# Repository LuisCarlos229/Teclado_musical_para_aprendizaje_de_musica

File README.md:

# Teclado musical para aprendizaje de música
 
Teclado sintetizador de bajo costo basado en ESP32, pensado para que niños aprendan música mediante un **modo aprendizaje** que guía la ejecución con LEDs.
 
Proyecto realizado en el marco de la asignatura **Proyecto Electrónico** de la Facultad de Ingeniería (FIO) – Universidad Nacional de Misiones (UNaM).

---
 
## Objetivos
 
Los objetivos planteados por la cátedra son:
 
- Diseñar y construir un teclado musical para el aprendizaje de música en niños, con tecnología transferible, de muy bajo costo y sin licencias de uso.
- Generar la documentación necesaria para su reproducción física.
- Emitir sonidos propios.
- Permitir cambiar parámetros musicales.
## Características
 
- 32 teclas con síntesis DDS por wavetables y salida I2S.
- Instrumentos activos: piano (Salamander Grand Piano) y guitarra.
- Modo aprendizaje: la tira LED WS2812B indica la nota a tocar y la canción avanza al ritmo del metrónomo, esperando a que se presione la nota correcta.
- Metrónomo configurable (3/4, 4/4, 5/4, 6/8, 7/8).
- Pantalla OLED con menú de configuración.
- Canciones permanentes en Flash y canciones adicionales en tarjeta SD (formato `.apr`).
## Estructura del repositorio
 
```
├── firmware/                       Código del ESP32 (ESP-IDF)
│   └── main/
│       ├── tasks/                  Tareas de FreeRTOS (audio, OLED, teclado, LEDs, SD, aprendizaje)
│       ├── notas/<instrumento>/    Wavetables y envolventes por instrumento (.h)
│       └── canciones/              Canciones permanentes en Flash (.h)
├── tools/
│   ├── wavetable_generator_octave/ Generación de wavetables y envolventes (Octave)
│   └── midi_processor_colab/       Conversión MIDI → .apr / .h (Python, Colab)
├── hardware/                       Proyecto KiCad: esquemáticos, PCB y lista de materiales
└── docs/                           manual de usuario e imágenes
```
 
## Flujo de trabajo
 
```
Grabaciones WAV/MP3 ──► Generador de wavetables (Octave) ──► .h de instrumentos ──┐
                                                                                  ├──► firmware (ESP-IDF) ──► ESP32
Archivos MIDI ────────► Procesador MIDI (Colab) ──► .h (Flash) ───────────────────┘
                                                └─► .apr ──► /APR en la tarjeta SD
```
 
## Requisitos
 
| Herramienta | Versión utilizada |
|---|---|
| ESP-IDF | v6.0.0 |
| GNU Octave | 11.1.0 (paquete `signal`) |
| Python | 3.x (Google Colab) con `mido` |
| KiCad | 9 |
 
## Uso rápido
 
### 1. Compilar y cargar el firmware
 
```bash
cd firmware
idf.py set-target esp32
idf.py build
idf.py -p PUERTO flash monitor
```
 
### 2. Generar wavetables de un instrumento
 
1. Colocar las grabaciones `.wav` del instrumento en `tools/wavetable_generator_octave/notas/<instrumento>/`.
2. Indicar el nombre del instrumento en `note_and_envelope_wavetable_generator.m` y ejecutarlo en Octave.
3. Copiar los `.h` generados en `notas/<instrumento>/salida_h/` a `firmware/main/notas/<instrumento>/`.
4. Agregar la carpeta en `INCLUDE_DIRS` de `firmware/main/CMakeLists.txt` y el instrumento en `firmware/main/tasks/Instrumentos.h`.
 
### 3. Convertir una canción MIDI
 
Abrir el notebook de [`tools/midi_processor_colab/`](tools/midi_processor_colab/) en Google Colab, cargar el `.mid` y elegir los canales a fusionar.
 
- Salida `.h` → `firmware/main/canciones/` (canción permanente en Flash).
- Salida `.apr` → carpeta `APR/` de la tarjeta SD.
### 4. Preparar la tarjeta SD
 
Formatear en FAT32, crear la carpeta `APR` en la raíz de la tarjeta y copiar ahí los `.apr` generados en el paso 3. El firmware busca las canciones en `/APR`.
 
## Hardware
 
| Bloque | Componentes principales |
|---|---|
| Control | ESP32 DevKit de 38 pines (CP2102) |
| Audio | DAC I2S PCM5102 + amplificador PAM8403 + altavoz de 4 Ω |
| Interfaz | Pantalla OLED I2C, tira LED WS2812B, expansor PCF8574 para pulsadores y LEDs |
| Teclado | Matriz de 32 teclas con diodos 1N4148 |
| Almacenamiento | Lector microSD |
| Alimentación | Fuente AC-DC Hi-Link HLK-10M05 (220 Vac → 5 V / 2 A) con fusible, regulador AMS1117-3.3 |
 
> **Precaución:** la placa trabaja con tensión de red de 220 Vac en la etapa de alimentación. Ensamblar y probar con las precauciones correspondientes, y montar el equipo en un gabinete cerrado antes de que lo usen niños.
 
El proyecto KiCad, el diagrama en bloques y la lista de materiales están en [`hardware/`](hardware/).
 
## Documentación
- Manual de usuario: [`docs/Manual_de_Usuario.pdf`](docs/Manual_de_Usuario.pdf).
## Créditos de muestras de audio
 
- **Salamander Grand Piano V3** – Alexander Holm ([sfzinstruments.github.io/pianos/salamander](https://sfzinstruments.github.io/pianos/salamander/)), licencia [CC BY 3.0](https://creativecommons.org/licenses/by/3.0/). Se usaron las muestras WAV de 16 bit a 44,1 kHz. Las wavetables y envolventes del firmware son obras derivadas: se extrajeron de esas grabaciones con el generador de Octave de este repositorio.
- **Philharmonia Sound Samples** – Philharmonia Orchestra ([philharmonia.co.uk/resources/sound-samples](https://philharmonia.co.uk/resources/sound-samples/)). Muestras de guitarra. Su licencia permite el uso libre, incluso comercial, siempre que las muestras no se vendan ni se distribuyan tal cual, ya sea como muestras o como instrumento de sampler.
> Por esta restricción, el repositorio **no incluye las grabaciones originales**. Solo incluye las wavetables y envolventes derivadas en formato `.h`. Para regenerarlas, descargá las muestras desde los sitios indicados y colocalas en `tools/wavetable_generator_octave/notas/<instrumento>/`.
 
## Créditos de canciones
 
### Canciones permanentes en Flash (`firmware/main/canciones/`)
 
| Canción | Origen de la melodía | Archivo |
|---|---|---|
| Estrellita | Melodía tradicional, dominio público | `cancion_estrellita.h` |
| Feliz cumpleaños | Melodía de *Good Morning to All*, M. J. y P. Hill, 1893, dominio público | `cancion_feliz_cumple.h` |
| Oda a la alegría | L. v. Beethoven, Sinfonía n.º 9, dominio público | `cancion_oda_alegria.h` |
| Para Elisa | L. v. Beethoven, WoO 59, dominio público | `cancion_para_elisa.h` |
 
## Bibliotecas de terceros
 
- **u8g2** – Oliver Kraus ([github.com/olikraus/u8g2](https://github.com/olikraus/u8g2)), licencia BSD de 2 cláusulas. Integrada mediante el componente ESP-IDF `nixy4/u8g2`.
- **led_strip** – Espressif Systems ([ESP Component Registry](https://components.espressif.com/components/espressif/led_strip)), licencia Apache 2.0.

## Autores

- Luis Carlos Hubner – [@LuisCarlos229](https://github.com/LuisCarlos229)
- Matias Emanuel Richart - [@MatiasRichart](https://github.com/MatiasRichart)

Cátedra de Proyecto Electrónico – FIO, UNaM.

## Licencias

Este proyecto se publica bajo licencias abiertas que permiten su uso, copia,
modificación, fabricación y comercialización sin pago de regalías:

| Contenido | Licencia | Archivo |
|---|---|---|
| Firmware ESP-IDF, scripts de Octave y Python | MIT | [LICENSE](LICENSE) |
| Hardware: esquemáticos, PCB, fabricación, BOM | CERN-OHL-P-2.0 | [hardware/LICENSE](hardware/LICENSE) |
| Documentación: manuales, guías, imágenes | CC BY 4.0 | [docs/LICENSE](docs/LICENSE) |
| Materiales de terceros: muestras de audio, librerías | Licencias propias | [NOTICE.md](NOTICE.md) |

Salvo que una carpeta tenga su propio archivo LICENSE, todo el contenido
original de este repositorio se publica bajo la licencia MIT.

## Aviso de responsabilidad

Este proyecto es un prototipo académico desarrollado en la Facultad de
Ingeniería de la Universidad Nacional de Misiones. Se entrega "tal cual",
sin garantía de ningún tipo. En la máxima medida permitida por la ley, los
autores no se responsabilizan por daños derivados de su fabricación, uso o
mal uso.

El dispositivo no está certificado como juguete según la normativa vigente.
Quien lo fabrique o distribuya es responsable de su seguridad y del
cumplimiento de las normas aplicables. Se recomienda su uso bajo
supervisión de un adulto.

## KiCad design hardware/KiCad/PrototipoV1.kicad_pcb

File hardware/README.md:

# Hardware — Teclado musical para aprendizaje de música

SPDX-License-Identifier: CERN-OHL-P-2.0
Copyright 2026 Luis Carlos Hubner, Matias Emanuel Richart
Source location: https://github.com/LuisCarlos229/Teclado_musical_para_aprendizaje_de_musica
Revisión: PrototipoV1

This source describes Open Hardware and is licensed under the CERN-OHL-P v2.

You may redistribute and modify this documentation and make products using it
under the terms of the CERN-OHL-P v2 (https://cern.ch/cern-ohl).

This documentation is distributed WITHOUT ANY EXPRESS OR IMPLIED WARRANTY,
INCLUDING OF MERCHANTABILITY, SATISFACTORY QUALITY AND FITNESS FOR A
PARTICULAR PURPOSE. Please see the CERN-OHL-P v2 for applicable conditions.

---

Los archivos de esta carpeta (esquemáticos y PCB en KiCad, archivos de
fabricación, lista de materiales y diseños mecánicos) se publican bajo la
licencia CERN-OHL-P v2, cuyo texto completo está en el archivo LICENSE de
esta misma carpeta. Pueden usarse, modificarse, fabricarse y comercializarse
libremente, conservando este aviso.

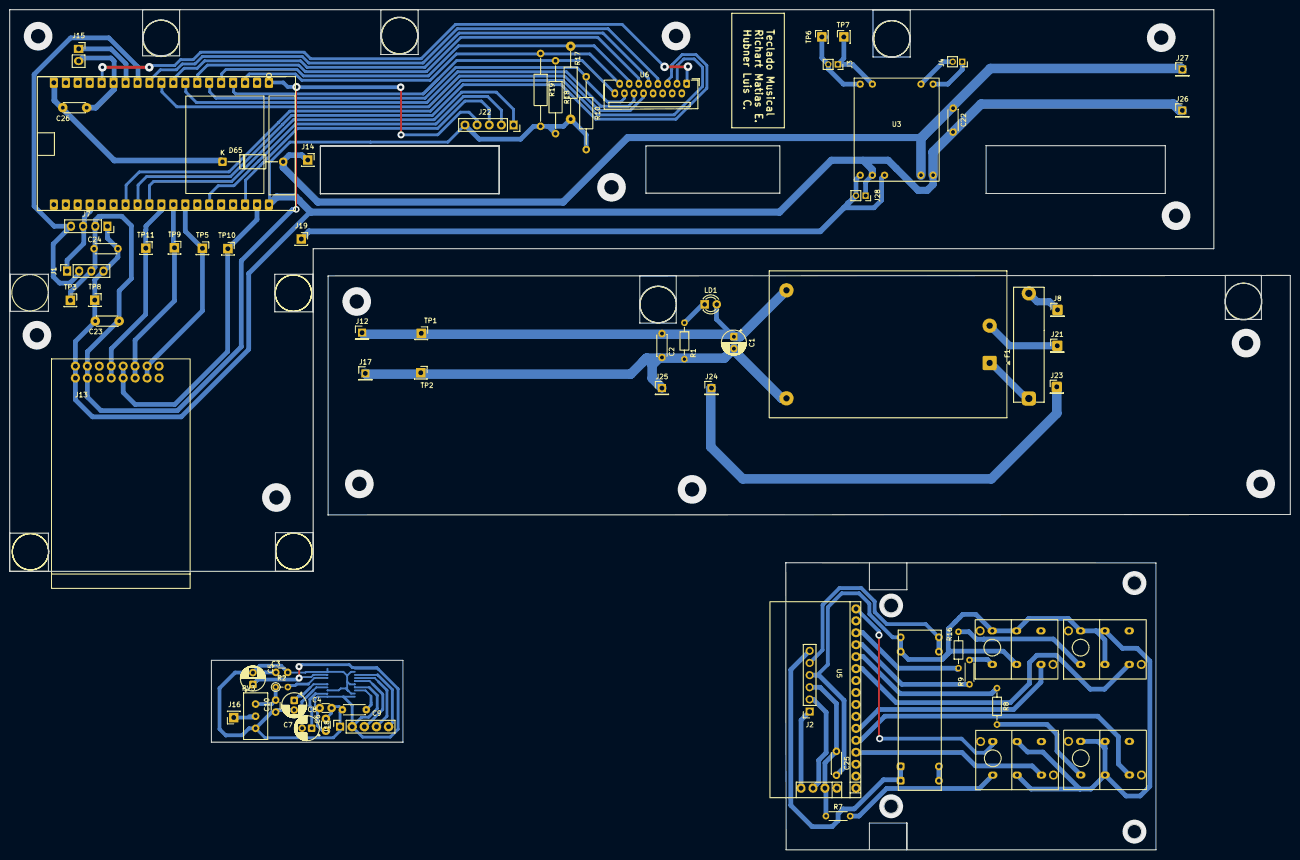
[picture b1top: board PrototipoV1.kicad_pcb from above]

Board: 2 copper layers, 267.9 x 175.7 mm, 72 parts (1 on the bottom side), 68 nets.

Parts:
C1, C5: 10u; CP_Radial_D5.0mm_P2.50mm
C2, C22, C23, C24, C25, C26: 0.1u; C_Disc_D4.3mm_W1.9mm_P5.00mm
C3, C4, C6: .1u; C_Disc_D3.0mm_W1.6mm_P2.50mm
C7, C8: 2.2u; CP_Radial_D5.0mm_P2.00mm
C9: .1u; C_Disc_D4.3mm_W1.9mm_P5.00mm
C10: 22n; C_Disc_D3.0mm_W1.6mm_P2.50mm
D65: Schottky; D_A-405_P12.70mm_Horizontal
F1: Fuse; FuseProye
J1, J7: Conn_01x04_Pin; PinSocket_1x04_P2.54mm_Vertical
J2: Conn_01x06_Pin; PinSocket_1x06_P2.54mm_Vertical
J3: Parlante2; PinSocket_1x02_P2.00mm_Vertical
J4: Parlante; PinSocket_1x02_P2.00mm_Vertical
J8, J24, J25: fase; PinHeader_1x01_P2.54mm_Vertical
J12, J27: VCC; PinHeader_1x01_P2.54mm_Vertical
J13: SD_Card_Device; SDCARD
J14, J16, J19: Conn_01x01_Pin; PinSocket_1x01_P2.54mm_Vertical
J15: Conn_01x02_Pin; PinSocket_1x02_P2.54mm_Vertical
J17, J26: GND; PinHeader_1x01_P2.54mm_Vertical
J18, J22: Conn_01x05_Pin; PinSocket_1x05_P2.54mm_Vertical
J21: neutro; PinHeader_1x01_P2.54mm_Vertical
J23: tierra; PinHeader_1x01_P2.54mm_Vertical
J28: JACK; PinSocket_1x02_P2.00mm_Vertical
LD1: LED; LED_D3.0mm
PS1: HLK-10M05; Converter_ACDC_Hi-Link_HLK-10Mxx
R1, R8, R16: 330; R_Axial_DIN0204_L3.6mm_D1.6mm_P7.62mm_Horizontal
R2: 470; R_Axial_DIN0204_L3.6mm_D1.6mm_P2.54mm_Vertical
R7, R9: 330; R_Axial_DIN0204_L3.6mm_D1.6mm_P5.08mm_Horizontal
R10, R17, R18, R19: 10k; R_Axial_DIN0207_L6.3mm_D2.5mm_P15.24mm_Horizontal
RV1: 10k; Potentiometer_deslizable_horizontal
RV3: 10k; Potentiometer_Bourns_3296W_Vertical
S1, S2, S3, S4: SP86
TP1: 5V; PinSocket_1x01_P2.54mm_Vertical
TP2: GND; PinSocket_1x01_P2.54mm_Vertical
TP3: TestPoint; PinSocket_1x01_P2.54mm_Vertical
TP5: SCK; PinSocket_1x01_P2.54mm_Vertical
TP6: L-; PinSocket_1x01_P2.54mm_Vertical
TP7: L+; PinSocket_1x01_P2.54mm_Vertical
TP8: GDN; PinSocket_1x01_P2.54mm_Vertical
TP9: MISO; PinSocket_1x01_P2.54mm_Vertical
TP10: MOSI; PinSocket_1x01_P2.54mm_Vertical
TP11: CS; PinSocket_1x01_P2.54mm_Vertical
U1: ESP32 CP2102; ESP32_38Pin
U2: PCM5102; TSSOP-20_4.4x6.5mm_P0.65mm
U3: pam8403
U5: modPCF8475
U6: CablePlanoP16

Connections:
+3V3: C23.1, C24.1, J1.3, J7.2, J13.2 (3V3), J22.4, TP3.1, U1.1 (3V3)
+5V: C22.1, D65.2 (A), J14.1, J27.1, U3.4 (Vin)
BCK: J22.1, U1.28 (GPIO17)
CS: J13.4 (CS), TP11.1, U1.29 (GPIO5)
DAT_IN: J15.1, U1.13 (GPIO12)
DIN: J22.2, U1.33 (GPIO21)
GND: C22.2, C23.2, C24.2, C26.2, J1.4, J7.1, J13.1 (GND), J15.2, J22.5, J26.1, J28.1, R10.2, R17.2, R18.2, R19.2, TP8.1, U1.14 (GND), U1.38 (GND), U3.2 (T), U3.5 (GND)
GND1: C3.2, C4.2, C5.2, C6.2, C8.2, C9.1, C10.2, J18.1, RV3.3, U2.3 (CPGND), U2.9 (AGND), U2.10 (DEMP), U2.12 (SCK), U2.16 (FMT), U2.19 (DGND)
GNDREF: C25.2, J2.4, RV1.3, S1.1 (C), S2.1 (C), S2.5 (K), S3.1 (C), S3.5 (K), S4.1 (C), S4.5 (K), U5.17 (GND)
GPIO4: U1.26 (GPIO4), U6.3
GPIO13: U1.15 (GPIO13), U6.1
GPIO16: U1.27 (GPIO16), U6.5
GPIO25: U1.9 (GPIO25), U6.9
GPIO26: U1.10 (GPIO26), U6.10
GPIO27: U1.11 (GPIO27), U6.7
GPIO32: U1.7 (GPIO32), U6.11
GPIO33: U1.8 (GPIO33), U6.12
GPIO34: R17.1, U1.5 (GPIO34), U6.13
GPIO35: R10.1, U1.6 (GPIO35), U6.14
GPIO36: R19.1, U1.3 (GPIO36), U6.15
GPIO39: R18.1, U1.4 (GPIO39), U6.16
GR: J23.1, J24.1
LD2: S1.5 (K), U5.16 (LED-K)
LD3: R8.1, U5.12 (P5)
LD4: R9.1, U5.13 (P6)
LD5: R16.1, U5.14 (P7)
LRCK: J22.3, U1.36 (GPIO22)
MISO: J13.7 (MISO), TP5.1, U1.31 (GPIO19)
MOSI: J13.5 (MOSI), TP10.1, U1.37 (GPIO23)
unnamed: C10.1, R2.1, RV3.1
unnamed: C26.1, D65.1 (K), U1.19 (V5)
unnamed: J3.1, TP7.1, U3.8 (L+)
unnamed: J3.2, TP6.1, U3.9 (L-)
unnamed: J4.1, U3.6 (R-)
unnamed: J4.2, U3.7 (R+)
unnamed: C1.1, C2.1, J12.1, LD1.2 (A), PS1.4 (+Vout), TP1.1
unnamed: C1.2, C2.2, J17.1, J25.1, PS1.3 (-Vout), R1.2, TP2.1
unnamed: J18.3, U2.15 (LRCK)
unnamed: J18.4, U2.14 (DIN)
unnamed: J18.5, U2.13 (BCK)
unnamed: LD1.1 (K), R1.1
unnamed: F1.1, PS1.1 (AC/L)
unnamed: R7.2, S1.4 (A)
unnamed: R8.2, S2.4 (A)
unnamed: R9.2, S3.4 (A)
unnamed: R16.2, S4.4 (A)
unnamed: C7.2, U2.4 (CAPM)
unnamed: C7.1, U2.2 (CAPP)
unnamed: C9.2, U2.18 (LDOO)
unnamed: R2.2, U2.7 (OUTR)
unnamed: C8.1, U2.5 (VNEG)
Neutro: J21.1, PS1.2 (AC/N)
P0: S1.3 (NO), U5.4 (P0)
P1: S2.3 (NO), U5.5 (P1)
P2: S3.3 (NO), U5.6 (P2)
P4: S4.3 (NO), U5.11 (P4)
Pot: J16.1, RV3.2
Pot2: J2.6, RV1.1
PotOut: J2.5, RV1.2
PotOut2: J19.1, J28.2, U3.1 (L), U3.3 (R)
SCK: J1.1, J7.3, U1.23 (GPIO15)
SCKi: J2.1, U5.20 (SCL)
SCKs: J13.6 (SCK), TP9.1, U1.30 (GPIO18)
SDA: J1.2, J7.4, U1.12 (GPIO14)
SDAi: J2.2, U5.19 (SDA)
VCC: C3.1, C4.1, C5.1, C6.1, J18.2, U2.1 (CPVDD), U2.8 (AVDD), U2.11 (FLT), U2.17 (XSMT), U2.20 (DVDD)
Vcc: C25.1, J2.3, R7.1, U5.18 (VCC)
fase: F1.2, J8.1

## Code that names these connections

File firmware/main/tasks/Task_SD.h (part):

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 *  CONEXIONES FÍSICAS (módulo SD por SPI — pines VSPI de fábrica, libres)
 *  ──────────────────────────────────────────────────────────────────────
 *  Módulo SD  →  ESP32
 *  MOSI       →  GPIO23
 *  MISO       →  GPIO19
 *  SCK        →  GPIO18
 *  CS         →  GPIO5
 *  VCC        →  3V3 (o 5V según módulo, revisar regulador on-board)
 *  GND        →  GND
 * =============================================================================
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
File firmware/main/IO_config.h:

/* =============================================================================
 *  IO_config.h  —  Configuración de pines y parámetros I2S/DMA
 *
 *  PCM5102A DAC via I2S  |  ESP-IDF v5.x
 *
 *  CONEXIONES FÍSICAS
 *  ──────────────────
 *  PCM5102A   →  ESP32
 *  BCK        →  PIN_I2S_BCK   (GPIO 17)
 *  LRCK/WS    →  PIN_I2S_LRCK  (GPIO 22)
 *  DIN        →  PIN_I2S_DATA  (GPIO 21)
 *  FMT        →  GND           (formato I2S estándar)
 *  XSMT       →  3V3           (sin mute)
 *  VCC        →  3V3
 *  GND        →  GND
 * =============================================================================
 */

#ifndef IO_CONFIG_H
#define IO_CONFIG_H

#include "driver/gpio.h"
#include "driver/i2s_std.h"

/* ──────────────────────────────────────────────────────────────
 *  PINES GPIO
 * ────────────────────────────────────────────────────────────── */
#define PIN_I2S_BCK     GPIO_NUM_17   /* Bit Clock                          */
#define PIN_I2S_LRCK    GPIO_NUM_22   /* Left/Right Clock (Word Select)     */
#define PIN_I2S_DATA    GPIO_NUM_21   /* Serial Data Out → DIN del PCM5102A */

//#define PIN_LED         GPIO_NUM_2   /* para prbar comunicacion entre tareas */

/* ──────────────────────────────────────────────────────────────
 *  PINES I2C
 * ────────────────────────────────────────────────────────────── */
#define OLED_PIN_SDA    GPIO_NUM_14
#define OLED_PIN_SCK    GPIO_NUM_15

/* ──────────────────────────────────────────────────────────────
 *  PARÁMETROS DE AUDIO
 * ────────────────────────────────────────────────────────────── */
#define SAMPLE_RATE_HZ   44100        /* Frecuencia de muestreo [Hz]        */
#define WAVETABLE_LEN    58

/* Polifonía máxima: notas que suenan a la vez. Acota la carga del núcleo 1
 * (elegido con Prueba_estres.h dejando margen). Si llega una nota más, se
 * roba una voz (ver voces_hacer_lugar() en Task_audio.h). Rango: 1 a 32. */
#ifndef MAX_VOCES
#define MAX_VOCES        14
#endif

/* ──────────────────────────────────────────────────────────────
 *  PARÁMETROS DEL DRIVER I2S / DMA
 * ────────────────────────────────────────────────────────────── */
#define DMA_BUF_FRAMES   512          /* Muestras por buffer DMA            */
#define DMA_BUF_COUNT    4            /* Número de buffers DMA en cola      */

/* ──────────────────────────────────────────────────────────────
 *  FUNCIÓN DE INICIALIZACIÓN I2S
 *  Crea y habilita el canal I2S TX en modo PLL (sin MCLK externo).
 *  Devuelve el handle del canal listo para usarse.
 * ────────────────────────────────────────────────────────────── */

static void gpio_init(void){
    //gpio_reset_pin(PIN_LED);
    //gpio_set_direction(PIN_LED,GPIO_MODE_OUTPUT);
    //gpio_set_pull_mode(PIN_LED, GPIO_PULLUP_ONLY);//para la pullup interna
    printf("==============  gpio_init finalizada =============== \n");
}

static inline i2s_chan_handle_t i2s_init(void)
{
    i2s_chan_handle_t tx_chan;

    /* Crear canal I2S TX */
    i2s_chan_config_t chan_cfg = I2S_CHANNEL_DEFAULT_CONFIG(I2S_NUM_0, I2S_ROLE_MASTER);
    chan_cfg.dma_desc_num  = DMA_BUF_COUNT;
    chan_cfg.dma_frame_num = DMA_BUF_FRAMES;

    ESP_ERROR_CHECK(i2s_new_channel(&chan_cfg, &tx_chan, NULL));

    /*  Configurar modo estándar I2S (formato Philips/I2S) */
    i2s_std_config_t std_cfg = {
        .clk_cfg = {
            .sample_rate_hz = SAMPLE_RATE_HZ,
            .clk_src        = I2S_CLK_SRC_DEFAULT,
            .mclk_multiple  = I2S_MCLK_MULTIPLE_256,
        },
        .slot_cfg = I2S_STD_PHILIPS_SLOT_DEFAULT_CONFIG(
                        I2S_DATA_BIT_WIDTH_16BIT,
                        I2S_SLOT_MODE_STEREO),
        .gpio_cfg = {
            .mclk = I2S_GPIO_UNUSED,    /* PLL interno: sin MCLK externo */
            .bclk = PIN_I2S_BCK,
            .ws   = PIN_I2S_LRCK,
            .dout = PIN_I2S_DATA,
            .din  = I2S_GPIO_UNUSED,
            .invert_flags = {
                .mclk_inv = false,
                .bclk_inv = false,
                .ws_inv   = false,
            },
        },
    };

    ESP_ERROR_CHECK(i2s_channel_init_std_mode(tx_chan, &std_cfg));

    /* Habilitar el canal (activa las señales de reloj) */
    ESP_ERROR_CHECK(i2s_channel_enable(tx_chan));

    return tx_chan;
}

#endif /* IO_CONFIG_H */
